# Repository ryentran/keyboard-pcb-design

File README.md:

# Keyboard PCB Design
This is a keyboard design for a 3x3 macropad created using KiCAD, Hasu's keyboard_parts [component library](https://github.com/tmk/kicad_lib_tmk) and [footprint library](https://github.com/tmk/keyboard_parts.pretty), and /u/techieee's [switch footprint library](https://github.com/egladman/keebs.pretty).

# Schematic

# PCB

# Soldered PCB
After creating the schematic and pcb design for the macropad, the pcb was printed using prototyping services ([JLCPCB](https://jlcpcb.com/)). Once the pcb was received, SMD components were handsoldered to the board and tested for functionaility.

# Programming
The MCU used for this project is an atmega32u4 which was programmed with [QMK_firmware](https://github.com/qmk/qmk_firmware). To achieve this, the used MCU pins and key layout was defined in C header files. Once everything was setup, the hexfile was generated using a makefile and loaded onto the MCU using [QMK_toolbox](https://github.com/qmk/qmk_toolbox). To test the board, the pins across each key was shorted with a wire and the programmed key was executed.

# Mechanical Key Switches
The switches use for this macropad are Zealios 62g lubed with Krytox 205 Grade 0

# Finished Product

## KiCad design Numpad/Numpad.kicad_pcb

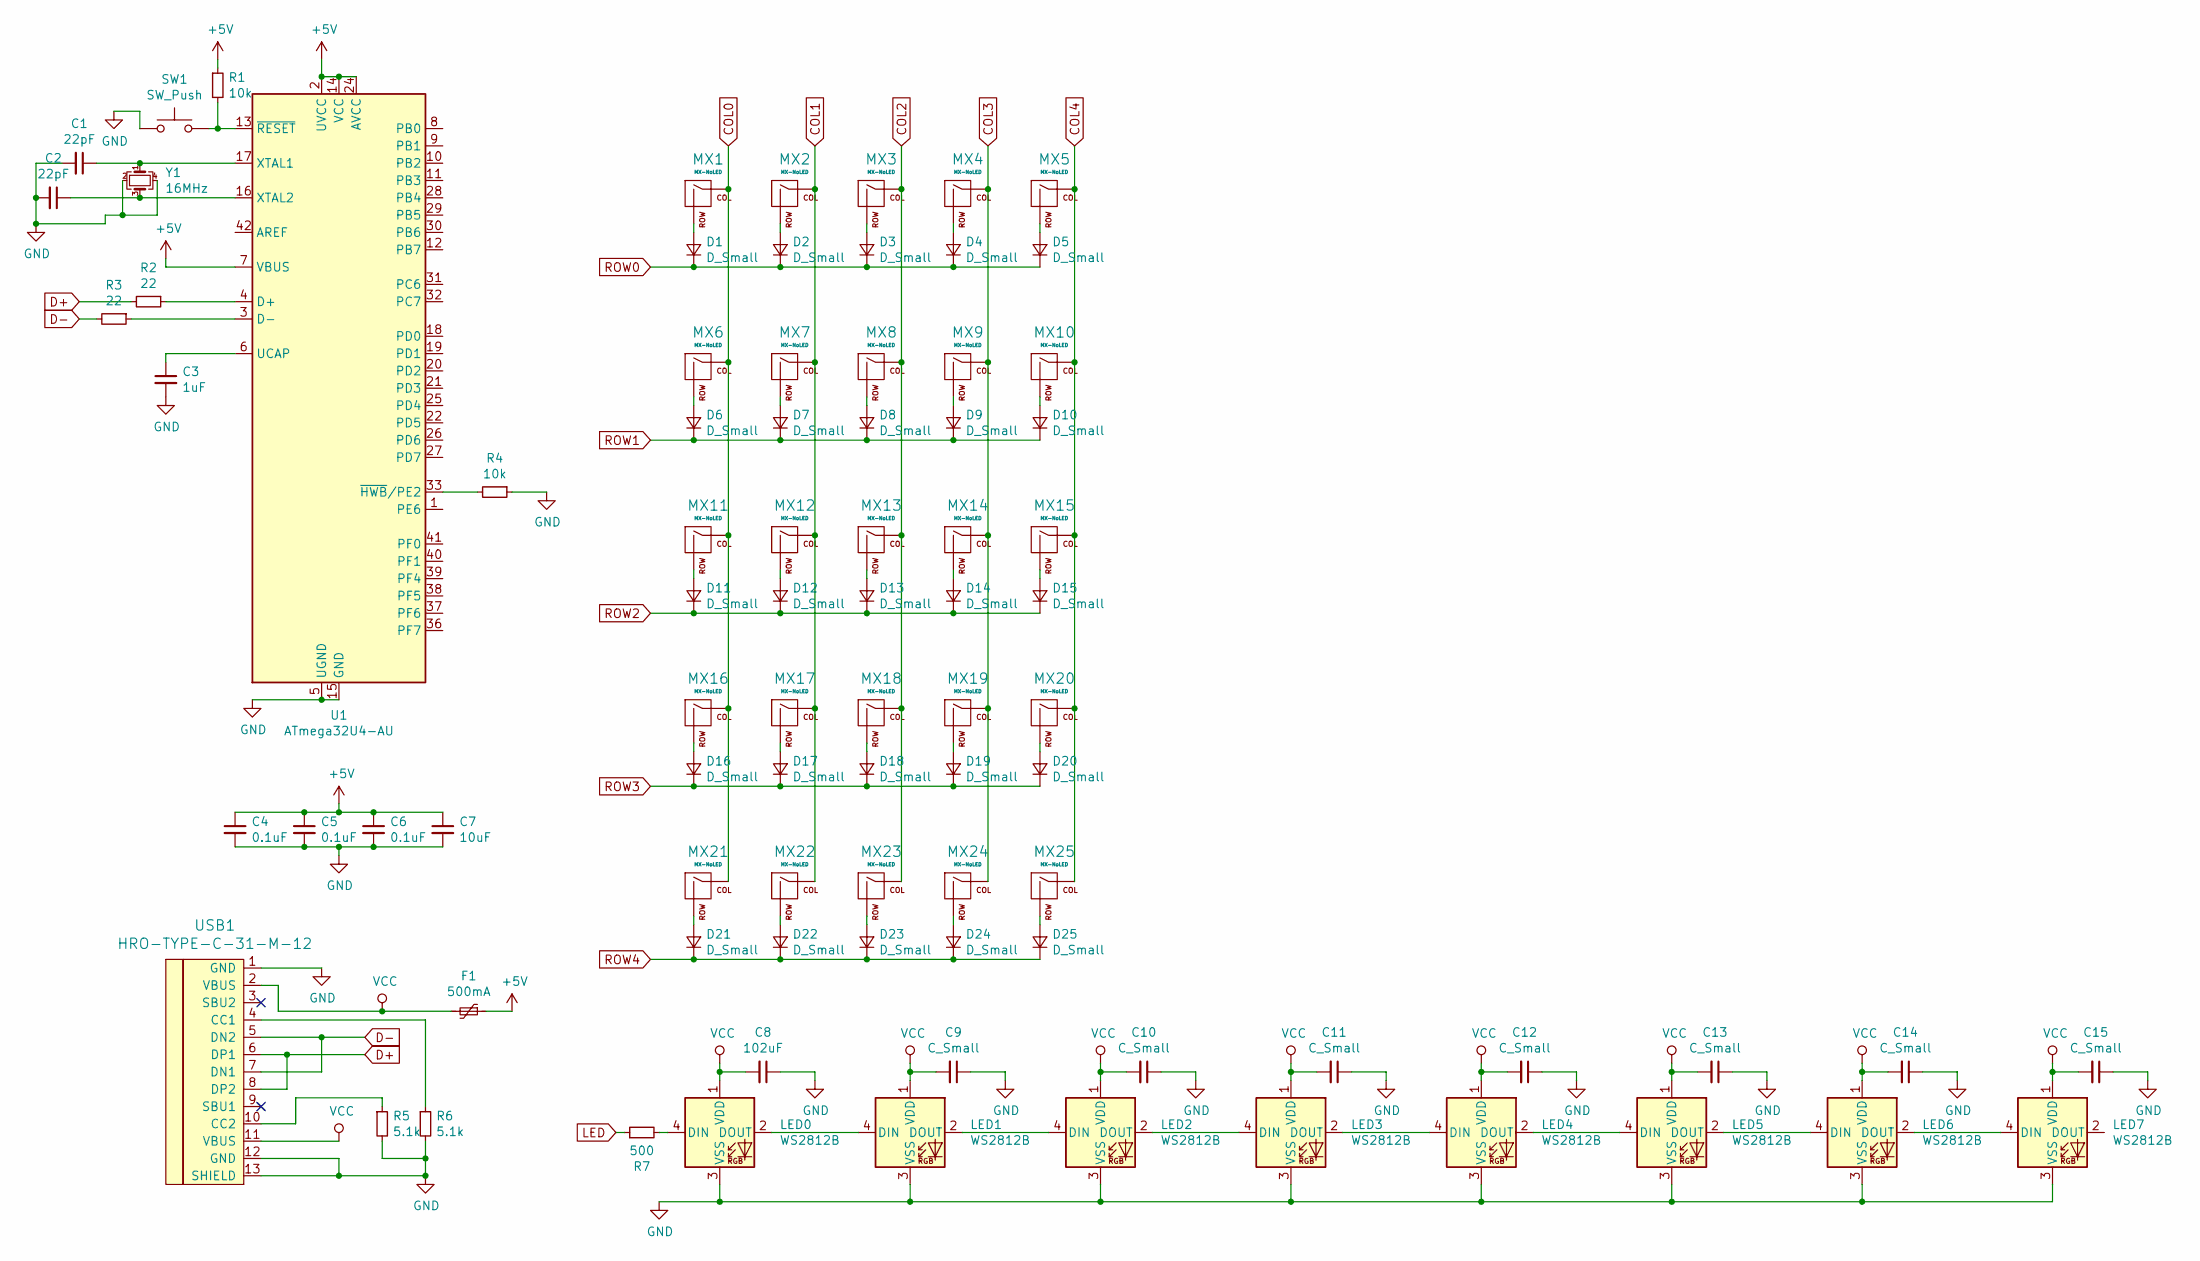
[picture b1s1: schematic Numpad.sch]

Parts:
C1, C2: 22pF; C_0805_2012Metric_Pad1.15x1.40mm_HandSolder
C3: 1uF; C_0805_2012Metric_Pad1.15x1.40mm_HandSolder
C4, C5, C6: 0.1uF; C_0805_2012Metric_Pad1.15x1.40mm_HandSolder
C7: 10uF; C_0805_2012Metric_Pad1.15x1.40mm_HandSolder
C8: 102uF; C_0805_2012Metric_Pad1.15x1.40mm_HandSolder
C9, C10, C11, C12, C13, C14, C15: C_Small; C_0805_2012Metric_Pad1.15x1.40mm_HandSolder
D1, D2, D3, D4, D5, D6, D7, D8, D9, D10, D11, D12, D13, D14, D15, D16, D17, D18, D19, D20, D21, D22, D23, D24, D25: D_Small; D_SOD-123
F1: 500mA; Fuse_1206_3216Metric_Pad1.42x1.75mm_HandSolder
LED0, LED1, LED2, LED3, LED4, LED5, LED6, LED7: WS2812B; LED_WS2812B_PLCC4_5.0x5.0mm_P3.2mm
MX1, MX2, MX3, MX4, MX5, MX6, MX7, MX8, MX9, MX10, MX11, MX12, MX13, MX14, MX15, MX16, MX17, MX18, MX19, MX20, MX21, MX22, MX23, MX24, MX25: MX-NoLED; MXOnly-1U-NoLED
R1, R4: 10k; R_0805_2012Metric_Pad1.15x1.40mm_HandSolder
R2, R3: 22; R_0805_2012Metric_Pad1.15x1.40mm_HandSolder
R5, R6: 5.1k; R_0805_2012Metric_Pad1.15x1.40mm_HandSolder
R7: 500; R_0805_2012Metric_Pad1.15x1.40mm_HandSolder
SW1: SW_Push; SKQG-1155865
U1: ATmega32U4-AU; TQFP-44_10x10mm_P0.8mm
USB1: HRO-TYPE-C-31-M-12; HRO-TYPE-C-31-M-12-HandSoldering
Y1: 16MHz; Crystal_SMD_3225-4Pin_3.2x2.5mm_HandSoldering

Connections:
+5V: C4.1, C5.1, C6.1, C7.1, F1.1, R1.1, U1.2 (UVCC), U1.7 (VBUS), U1.14 (VCC), U1.24 (AVCC), U1.34 (VCC), U1.44 (AVCC)
COL0: MX1.1 (COL), MX6.1 (COL), MX11.1 (COL), MX16.1 (COL), MX21.1 (COL), U1.41 (PF0)
COL1: MX2.1 (COL), MX7.1 (COL), MX12.1 (COL), MX17.1 (COL), MX22.1 (COL), U1.40 (PF1)
COL2: MX3.1 (COL), MX8.1 (COL), MX13.1 (COL), MX18.1 (COL), MX23.1 (COL), U1.28 (PB4)
COL3: MX4.1 (COL), MX9.1 (COL), MX14.1 (COL), MX19.1 (COL), MX24.1 (COL), U1.27 (PD7)
COL4: MX5.1 (COL), MX10.1 (COL), MX15.1 (COL), MX20.1 (COL), MX25.1 (COL), U1.26 (PD6)
D+: R2.2, USB1.6 (DP1), USB1.8 (DP2)
D-: R3.2, USB1.5 (DN2), USB1.7 (DN1)
GND: C1.2, C2.2, C3.2, C4.2, C5.2, C6.2, C7.2, C8.1, C9.1, C10.1, C11.1, C12.1, C13.1, C14.1, C15.1, LED0.3 (VSS), LED1.3 (VSS), LED2.3 (VSS), LED3.3 (VSS), LED4.3 (VSS), LED5.3 (VSS), LED6.3 (VSS), LED7.3 (VSS), R4.1, R5.2, R6.2, SW1.1, U1.5 (UGND), U1.15 (GND), U1.23 (GND), U1.35 (GND), U1.43 (GND), USB1.1 (GND), USB1.12 (GND), USB1.13 (SHIELD), Y1.2, Y1.4
LED: R7.1, U1.25 (PD4)
unnamed: C1.1, U1.17 (XTAL1), Y1.1
unnamed: C2.1, U1.16 (XTAL2), Y1.3
unnamed: C3.1, U1.6 (UCAP)
unnamed: D1.2 (A), MX1.2 (ROW)
unnamed: D2.2 (A), MX2.2 (ROW)
unnamed: D3.2 (A), MX3.2 (ROW)
unnamed: D4.2 (A), MX4.2 (ROW)
unnamed: D5.2 (A), MX5.2 (ROW)
unnamed: D6.2 (A), MX6.2 (ROW)
unnamed: D7.2 (A), MX7.2 (ROW)
unnamed: D8.2 (A), MX8.2 (ROW)
unnamed: D9.2 (A), MX9.2 (ROW)
unnamed: D10.2 (A), MX10.2 (ROW)
unnamed: D11.2 (A), MX11.2 (ROW)
unnamed: D12.2 (A), MX12.2 (ROW)
unnamed: D13.2 (A), MX13.2 (ROW)
unnamed: D14.2 (A), MX14.2 (ROW)
unnamed: D15.2 (A), MX15.2 (ROW)
unnamed: D16.2 (A), MX16.2 (ROW)
unnamed: D17.2 (A), MX17.2 (ROW)
unnamed: D18.2 (A), MX18.2 (ROW)
unnamed: D19.2 (A), MX19.2 (ROW)
unnamed: D20.2 (A), MX20.2 (ROW)
unnamed: D21.2 (A), MX21.2 (ROW)
unnamed: D22.2 (A), MX22.2 (ROW)
unnamed: D23.2 (A), MX23.2 (ROW)
unnamed: D24.2 (A), MX24.2 (ROW)
unnamed: D25.2 (A), MX25.2 (ROW)
unnamed: LED0.2 (DOUT), LED1.4 (DIN)
unnamed: LED0.4 (DIN), R7.2
unnamed: LED1.2 (DOUT), LED2.4 (DIN)
unnamed: LED2.2 (DOUT), LED3.4 (DIN)
unnamed: LED3.2 (DOUT), LED4.4 (DIN)
unnamed: LED4.2 (DOUT), LED5.4 (DIN)
unnamed: LED5.2 (DOUT), LED6.4 (DIN)
unnamed: LED6.2 (DOUT), LED7.4 (DIN)
unnamed: R1.2, SW1.2, U1.13 (~RESET)
unnamed: R2.1, U1.4 (D+)
unnamed: R3.1, U1.3 (D-)
unnamed: R4.2, U1.33 (~HWB~/PE2)
unnamed: R5.1, USB1.10 (CC2)
unnamed: R6.1, USB1.4 (CC1)
ROW0: D1.1 (K), D2.1 (K), D3.1 (K), D4.1 (K), D5.1 (K), U1.10 (PB2)
ROW1: D6.1 (K), D7.1 (K), D8.1 (K), D9.1 (K), D10.1 (K), U1.8 (PB0)
ROW2: D11.1 (K), D12.1 (K), D13.1 (K), D14.1 (K), D15.1 (K), U1.39 (PF4)
ROW3: D16.1 (K), D17.1 (K), D18.1 (K), D19.1 (K), D20.1 (K), U1.38 (PF5)
ROW4: D21.1 (K), D22.1 (K), D23.1 (K), D24.1 (K), D25.1 (K), U1.37 (PF6)
VCC: C8.2, C9.2, C10.2, C11.2, C12.2, C13.2, C14.2, C15.2, F1.2, LED0.1 (VDD), LED1.1 (VDD), LED2.1 (VDD), LED3.1 (VDD), LED4.1 (VDD), LED5.1 (VDD), LED6.1 (VDD), LED7.1 (VDD), USB1.2 (VBUS), USB1.11 (VBUS)

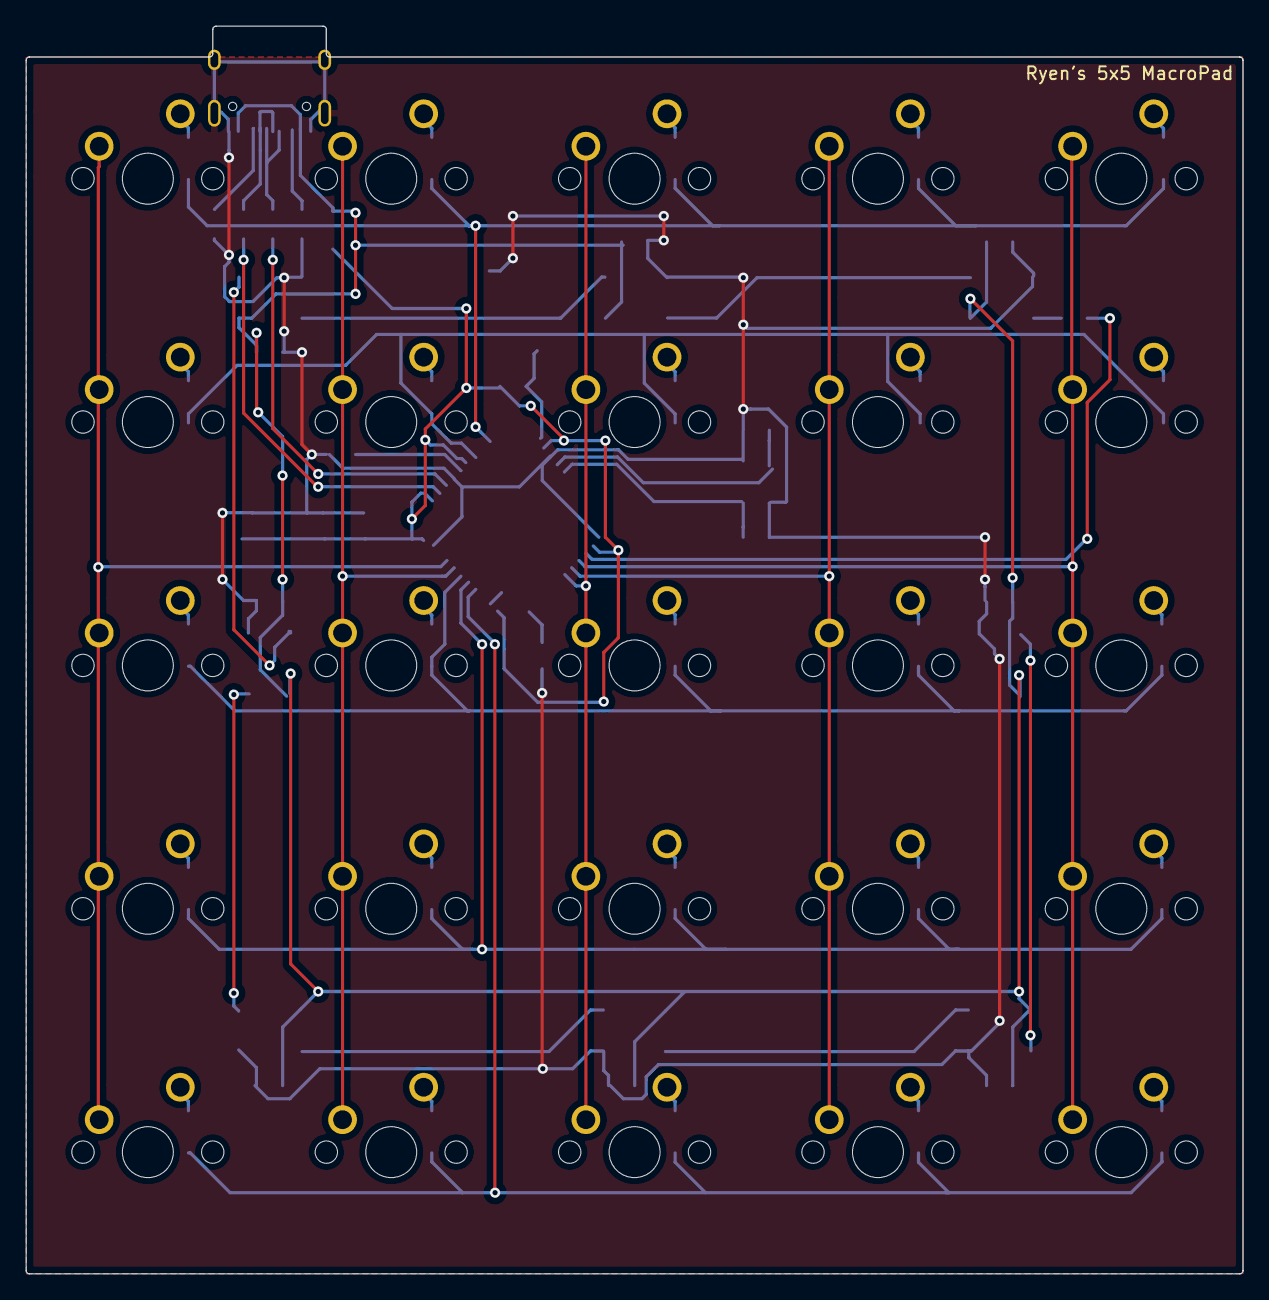
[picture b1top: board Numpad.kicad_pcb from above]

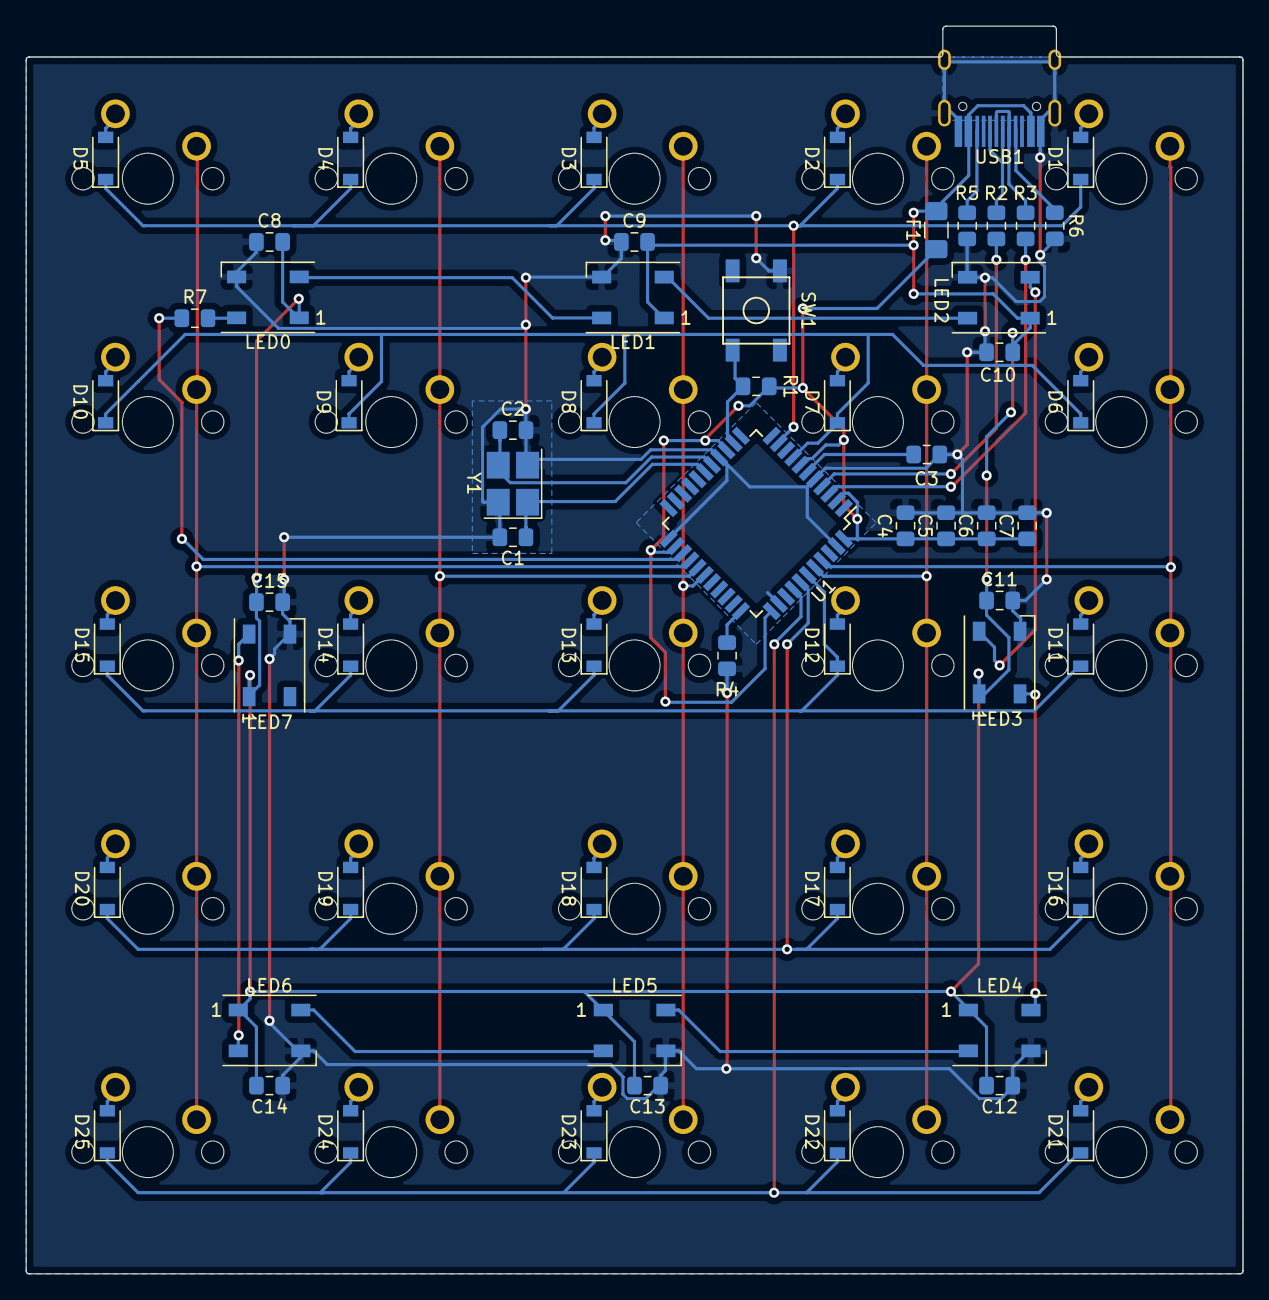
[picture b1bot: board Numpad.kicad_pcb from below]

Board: 2 copper layers, 95.2 x 97.7 mm, 85 parts (60 on the bottom side), 58 nets.

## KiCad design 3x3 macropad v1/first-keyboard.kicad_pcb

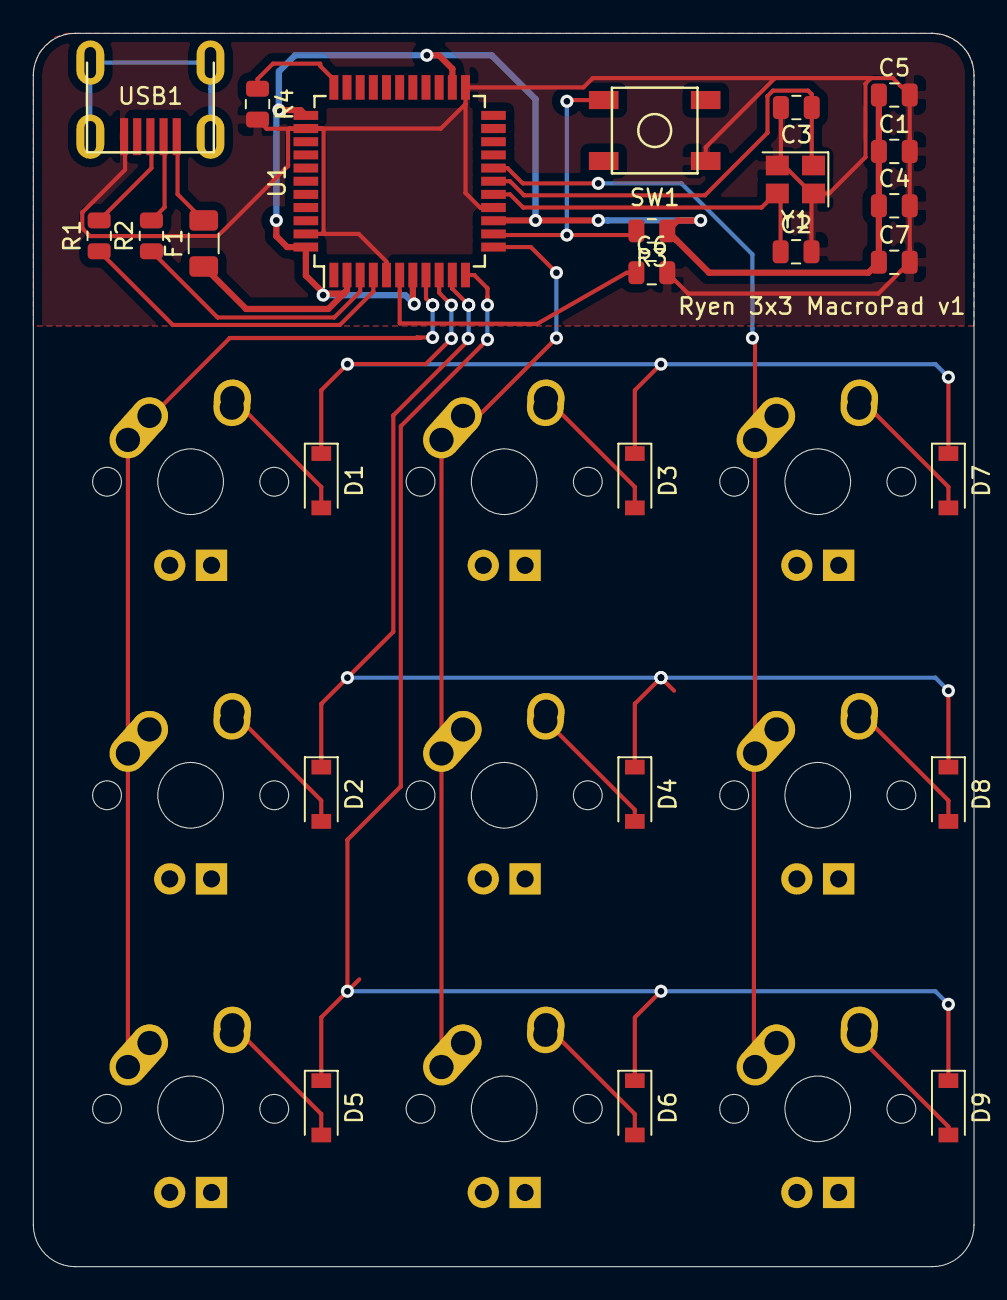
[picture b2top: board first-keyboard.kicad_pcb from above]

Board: 2 copper layers, 57.2 x 74.9 mm, 34 parts (0 on the bottom side), 27 nets.

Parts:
C1, C4, C5, C7: 0.1uF; C_0805_2012Metric
C2, C3: 22pF; C_0805_2012Metric
C6: 1uF; C_0805_2012Metric
D1, D2, D3, D4, D5, D6, D7, D8, D9: SOD-123; D_SOD-123
F1: Polyfuse; Fuse_1206_3216Metric
MX1, MX2, MX3, MX4, MX5, MX6, MX7, MX8, MX9: MX-NoLED; MX-1U
R1, R2: 22; R_0805_2012Metric
R3, R4: 10k; R_0805_2012Metric
SW1: SW_Push; SKQG-1155865
U1: ATmega32U4-AU; TQFP-44_10x10mm_P0.8mm
USB1: Molex-0548190589
Y1: 16MHz; Crystal_SMD_3225-4Pin_3.2x2.5mm

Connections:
+5V: C1.1, C4.1, C5.1, C7.1, F1.1, R3.1, U1.2, U1.7, U1.14, U1.24, U1.34, U1.44
COL0: MX1.1, MX4.1, MX7.1, U1.8
COL1: MX2.1, MX5.1, MX8.1, U1.12
COL2: MX3.1, MX6.1, MX9.1, U1.18
D+: R1.2, USB1.3
D-: R2.2, USB1.4
GND: C1.2, C2.2, C3.2, C4.2, C5.2, C6.2, C7.2, R4.2, SW1.1, U1.5, U1.15, U1.23, U1.35, U1.43, USB1.1, Y1.2, Y1.4
unnamed: C2.1, U1.16, Y1.3
unnamed: C3.1, U1.17, Y1.1
unnamed: C6.1, U1.6
unnamed: D1.2, MX1.2
unnamed: D2.2, MX4.2
unnamed: D3.2, MX2.2
unnamed: D4.2, MX5.2
unnamed: D5.2, MX7.2
unnamed: D6.2, MX8.2
unnamed: D7.2, MX3.2
unnamed: D8.2, MX6.2
unnamed: D9.2, MX9.2
unnamed: R1.1, U1.4
unnamed: R2.1, U1.3
unnamed: R3.2, SW1.2, U1.13
unnamed: R4.1, U1.33
ROW0: D1.1, D3.1, D7.1, U1.9
ROW1: D2.1, D4.1, D8.1, U1.10
ROW2: D5.1, D6.1, D9.1, U1.11
VCC: F1.2, USB1.5

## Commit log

2019-08-05 added submodules
2019-08-05 added libraries to project
2019-08-06 3x3 macropad v1
2019-08-06 renamed project
2019-08-11 Fixed schematic, added QMK Firmware
2019-08-11 Generated hexfile, sucessfully flashed hex to atmega32u4
2019-08-11 Created readme
2019-08-11 Added images
2019-08-11 rm qmk_firmware
2019-08-11 added qmk_firmware
2019-08-11 added image
2019-08-14 added usb c library, eemr tkl project
2019-08-14 completed schematic for tkl
2019-08-14 removed empty directory
2019-08-21 new projects
2019-08-28 numpad/5x5 macropad project
2019-09-01 finished pcb routing
2020-02-06 modified directories
2020-05-06 Alice pcb, created schematic symbols
